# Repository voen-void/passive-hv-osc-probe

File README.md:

# Passive High Voltage oscilloscope probe

> [!IMPORTANT]
> **UNTESTED!**
> **This project is still under construction and has not yet been electrically tested. The stated voltage ratings are design targets, not verified operating limits. It is not recommended to build this currently!**

[Schematic pdf](/images/hv-probe-passive-schematic.pdf) included in the repo.

*Summary:*
This is a 1000:1 passive high-voltage oscilloscope probe designed for measurements up to 20 kV peak. The probe uses a compensated resistive/capacitive divider, a shielded and resin-potted PCB construction, and is designed to fit inside a 37.6 mm ID metal tube. (1-1/2" tubing will do fine here) The achieveable bandwidth is around XX MHz.

## TLDR
| Parameter                    | Value             |
| ---------------------------- | ----------------- |
| Attenuation                  | 1000:1            |
| Maximum recommended voltage  | 20 kV peak        |
| Divider                      | 50 MΩ / 50 kΩ     |
| Probe body                   | Resin-potted PCB  |
| Shield                       | Brass/copper tube |
| Shield inner diameter        | 37.6 mm (1.48 in) |
| PCB                          | 2-layer           |
| Recommended potting resin εr | ≤ 6               |
| Compensation                 | Adjustable        |
| bandwidth                    | XX MHz            |
| Status                       | **Not yet tested**|

The design is based on a [EEVBlog Video](https://www.youtube.com/watch?v=jUvSP3BQpvs). The electrical design is done in [KiCad](https://www.kicad.org/) 10.0.6, and the mechanical design is done in [onshape](https://www.onshape.com/en/). The total cost of a single probe adds up to around **100 USD**, though it will be larger because not all parts can be bought in small enough quantities (eg. the resin, the PCBs \[usually 5 minimum\] and the shielding tube).

> [!NOTE]
> The PCBs for this project have been provided by [PCBWay](https://www.pcbway.com/).

## What is it?
This project tackles the design of a simple high voltage oscilloscope probe based on the principles of a voltage divider. The simplest schematic would look like this:

<!--

-->

But it's a bit more complex than that if we want to probe AC signals of considerable frequency. The parasitic capacitances need to be compensated to achieve better bandwidth. For this reason the resistors forming the voltage divider are bypassed by capacitors which increase the AC transmittance of the circuit.

<!--

-->

The capacitance values presented in the above schematic are just for reference, and will likely be different for the actual probe. For a compensated probe the transmittance of just the resistors should match that of just the capacitors. If we cared only to measure DC, then the capacitors could be ommited entirely.

At the low voltage end two footprints for capacitors are provided which allow simple compensation as you will need to adjust that capacitance to achieve a flat frequency response. Capacitor values are also proposed, but the final capacitor value may differ from the proposed value because the parasitic capacitance depends on the PCB, components, potting compound and mechanical construction.
For adjusting the DC and low frequency transmittance a 10 turn potentiometer is provided. It should be set to 1 MΩ (full range) by default. While calibrating adjust it to reach desired 1000:1 division ratio. Then the capacitor should be adjusted to achieve flat frequency response. A proposed calibration procedure follows;

### Calibration

The proposed calibration procedure:
1. Set the 10-turn potentiometer to 1 MΩ.
2. Apply a suitable low-voltage signal.
3. Adjust the potentiometer until the DC attenuation is 1000:1.
4. Apply a square-wave calibration signal.
5. Adjust the compensation capacitor(s) for the flattest frequency response.
6. Verify the response at multiple frequencies.

## Safety

> [!CAUTION]
> High voltages can easily be lethal. Only deal with them if you are qualified. You are building and using this project at your own risk! This is experimental high-voltage equipment.

1. Do not use the probe on energized equipment unless you are qualified to work with high voltage.
2. The 20 kV value is currently a design target, not a verified rating.
3. Never rely on the probe alone to provide isolation.
4. Use an appropriate current-limited HV source during testing.
5. Ensure the oscilloscope and all connected equipment are rated appropriately.
6. The metal shield must be properly grounded.
7. Inspect the probe for mechanical damage before use.
8. Do not use a probe that has experienced an internal arc-over.
7. Potting compound can make internal failures difficult or impossible to inspect.

The maximum recommended voltage which this probe can measure is 20 kV **peak**. The components should handle 50 kV, but the final breakdown voltage depends on the quality of your craftsmanship - primarly the resin used, how clean the elements were when casting them in resin, if there are any air bubbles trapped inside the resin (**there shouldn't be any!**). A safety margin must be used!

### Internal arc-over protection

For increased safety a microwave fuse may be added in series with the input of the probe. This way if an over-current condition occurs - indicating an internal arc over - the fuse will open indicating thus. Microwave fuses are the highest voltage rated fuses I could cheaply find, and should do the job. A lower current fuse would be ideal, but those only come with voltage ratings up to 250 VAC. The reason for that fuse is to protect the probe in the case of an internal arc-over. If an arc over was to happen inside the probe, excessive current would be drawn from DUT (if DUT can provide it). Sustained internal arcing might lead to pressure buildup inside the probe body, which due to it's construction could become very dangerous. In an extreme scenario the probe could explode causing harm to everything around it. For this reason it is recommended to use some sort of fuse in series with the probe input, and it it blows, the probe should no longer be used and should be marked as faulty and discarded. High voltage apparatus potted in hard resin is known to pose this kind of danger and should be handled accordingly.

## Physical construction

[A drawing with the dimensions](/images/hv-probe-passive-dimensions.pdf) of the PCB included in the repo.

The probe requires some special attention when it comes to construction. Since the divider consists of such high value resistors (50 MΩ to 50 kΩ divider), it's sensitive to interference. For this reason the probe is designed to fit in a shield in the form of a brass or copper tube of the inner diameter of 37,6 mm (1.48 in). This shield shall be grounded to protect the sensitive signal inside. To increase dielectric breakdown a special resin must be used, and the PCB inside the shield should be cast in it. Since the voltages measured are significant, leaving the PCB in the free air wont cut it. Try to pick a resing with as low dielectric constant as possible. [HUNTSMAN CW5620 BLUE](https://products.huntsman.com/products/arathane-cw-5620-hy-5610) was used, which has a relative dielectric constant of 6. It is recommended to not use resins of higher relative dielectric constant as it increase the parasitic capacitances, which will degrade the bandwidth of the probe cutting down high frequency transmittance.

### Cost of building a single probe

| Element (MPN)                | Reference     | Qty.  | Price \[USD\] |
| --------------------------   | ------------- | ----- | ----------- |
| PCB                          | -             | 1     | 4.2         |
| [564RC0GAJ602EJ240J](https://mou.sr/46weVJR)           | C1-C5, C8-C12 | 10    | 30.27       |
| [VJ1206A222FFBAT](https://mou.sr/3SJN9Gu)              | C6, C7        | 2     | 2.55        |
| [112413](https://mou.sr/46wNFuQ)                       | J2            | 1     | 8.22        |
| [VR68000001005JAC00](https://mou.sr/3V2SlWK)           | R1-R5         | 5     | 7.02        |
| [CR1206-FX-5602ELF](https://mou.sr/3SBNyLk)            | R6            | 1     | 0.1         |
| [3296Z-1-105LF](https://mou.sr/4zNrIVU)                | RV1           | 1     | 2.45        |
| HUNTSMAN CW5620 BLUE Resin   | -             | 732 g | 25          |
| Copper shielding tube        | -             | 15 cm | 17          |
| 3DP filament cost            | -             | -     | 2           |

Total: 98.81 USD without shipping for a single probe. Both the PCBs, the resin and the shielding tube only come in larger quantities than needed for the project, thus the actual price may be higher depending on what you are able to source.

### PCB

The PCB has been designed to be a simple two-layer board. Soldermask has been removed from the part of the PCB that shall be submerged in isolating resin. The part of the PCB that has soldermask left should be left sticking out of the resin to allow for adjustments of the compensation capacitors and resistor if needed. A solder pad connected to probe ground is exposed to facilitate an easy connection to the shield.

The PCB has been designed with a specific kind of HV terminal construction. A large portion of copper is exposed at the HV end of the probe with a long distance separating it from the shield, to increase creepage distance. This part of the probe (tapered end) should be exposed from the shield and should be cast in resin, preferably in a ribbed shape for further increase of creepage distance. Before casting the PCB a brass piece shall be machined such that it fits over the straight tip of the tapored end of the PCB and presents a female thread at the end, into which a screw may be threaded into to make electrical contact. This piece should be soldered to the tapored tip of the PCB before casting. It should be noted that **no excessive force** should be used on this part of the probe in relation to the probe body. To make fastening easier the exposed part of the brass piece may be shaped in a way which enables holding it with an appropirately sized wrench. In such case a wrench may be used to hold the HV terminal of the probe down while fastening an attachment to it. The end piece should only be tightened finger-tight.

#### The manufactured PCB

I had the PCB manufactured by [PCBWay](https://www.pcbway.com/). The process was very simple: I uploaded the gerbers, placed a Quick Order and the PCBs (five of them!) arrived at my doorstep in a couple of days. I was pleasantly surprised by the packing quality and the PCB manufacture quality was excellent, picture below!

After receiving the PCB i shortly proceeded to populating it with components. [Assembly drawings](/images/hv-probe-passive-assembly.pdf) included in the repo.

### Notes on elements used

The resistors used for the high voltage part of the voltage divider are special high voltage resistors, which may operate up to 10 kV across them. The capacitors used in the divider are all C0G / NP0 dielectric capacitors, for increased  temperature stability. other dielectrics may be used, but it's strongly recommended to use Class I dielectric materials, preferably C0G / NP0 as it will cause the smallest drift in alignment over a wide range of temperatures.

### Casting in resin

To cast the probe in resin a CAD model for a 3D-printable mold has been made in [onshape](https://cad.onshape.com/documents/634b2c7804eb6959816cbee4/w/1f30c7d8f223e5e8fad3fc6d/e/e251d38d61b503254921d7bb). 

<!--

-->

Recommended material for the mold is PETG, as it's recommended for molding and should allow for easier separation after casting. The two mold halves are to be screwed together by 18 70 mm long M4 bolts. Wax was used as mold release. The resin should be poured down into the metal tube, with the tip of the probe facing downwards. Resin should be added until it fills up the mold up to the top 3 mm venting holes.

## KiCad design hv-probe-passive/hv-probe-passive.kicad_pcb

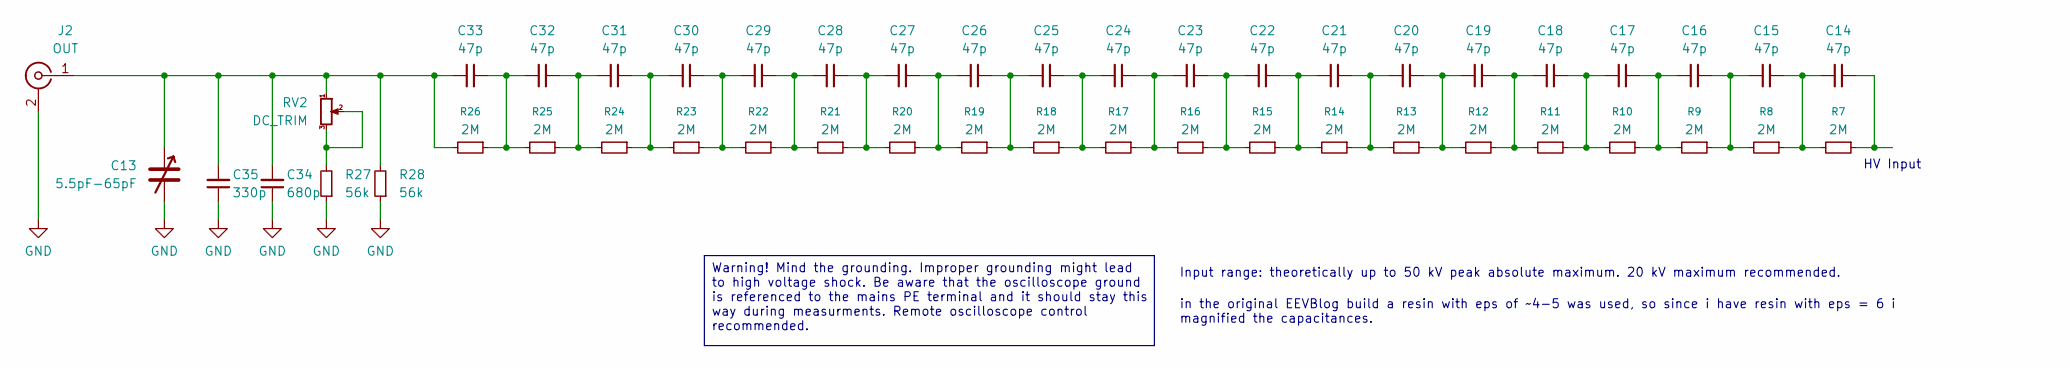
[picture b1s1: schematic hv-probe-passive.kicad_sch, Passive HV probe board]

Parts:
C13: 5.5pF-65pF; BFC2808 P5.0x7.5mm; LCSC C3273327
C14, C15, C16, C17, C18, C19, C20, C21, C22, C23, C24, C25, C26, C27, C28, C29, C30, C31, C32, C33: 47p; C_1808_4520Metric; LCSC C2958815
C34: 680p; C_1206_3216Metric; MPN AC1206JRNPOBBN681; LCSC C3871624
C35: 330p; C_1206_3216Metric; MPN 1206CG331J101NT
J2: OUT; BNC_Amphenol_B6252HB-NPP3G-50_Horizontal; MPN 112413
R7, R8, R9, R10, R11, R12, R13, R14, R15, R16, R17, R18, R19, R20, R21, R22, R23, R24, R25, R26: 2M; R_2512_6332Metric; LCSC C2779442
R27, R28: 56k; R_0805_2012Metric; LCSC C17756
RV2: DC_TRIM; Potentiometer_Bourns_3296X_Horizontal; LCSC C49190482

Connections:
GND: C13.2, C34.1, C35.1, J2.2 (Ext), R27.1, R28.1
unnamed: C14.1, R7.1
unnamed: C14.2, C15.1, R7.2, R8.1
unnamed: C15.2, C16.1, R8.2, R9.1
unnamed: C16.2, C17.1, R9.2, R10.1
unnamed: C17.2, C18.1, R10.2, R11.1
unnamed: C18.2, C19.1, R11.2, R12.1
unnamed: C19.2, C20.1, R12.2, R13.1
unnamed: C20.2, C21.1, R13.2, R14.1
unnamed: C21.2, C22.1, R14.2, R15.1
unnamed: C22.2, C23.1, R15.2, R16.1
unnamed: C23.2, C24.1, R16.2, R17.1
unnamed: C24.2, C25.1, R17.2, R18.1
unnamed: C25.2, C26.1, R18.2, R19.1
unnamed: C26.2, C27.1, R19.2, R20.1
unnamed: C27.2, C28.1, R20.2, R21.1
unnamed: C28.2, C29.1, R21.2, R22.1
unnamed: C29.2, C30.1, R22.2, R23.1
unnamed: C30.2, C31.1, R23.2, R24.1
unnamed: C31.2, C32.1, R24.2, R25.1
unnamed: C32.2, C33.1, R25.2, R26.1
unnamed: C13.1, C33.2, C34.2, C35.2, J2.1 (In), R26.2, R28.2, RV2.1
unnamed: R27.2, RV2.2, RV2.3

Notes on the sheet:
HV Input
in the original EEVBlog build a resin with eps of ~4-5 was used, so since i have resin with eps = 6 i magnified the capacitances.
Warning! Mind the grounding. Improper grounding might lead to high voltage shock. Be aware that the oscilloscope ground is referenced to the mains PE terminal and it should stay this way during measurments. Remote oscilloscope control recommended.
Input range: theoretically up to 50 kV peak absolute maximum. 20 kV maximum recommended.

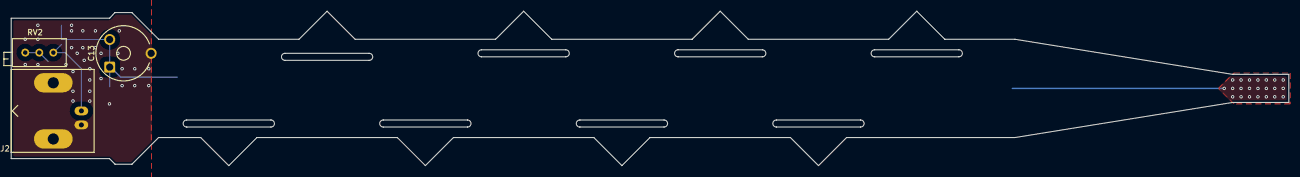
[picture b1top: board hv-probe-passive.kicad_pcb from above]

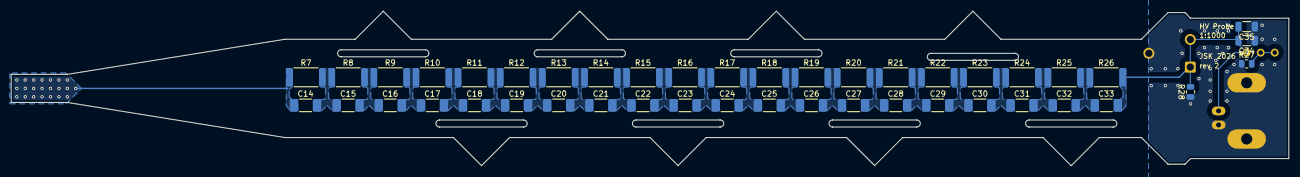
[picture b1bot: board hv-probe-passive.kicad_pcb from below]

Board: 2 copper layers, 231.1 x 27.9 mm, 47 parts (44 on the bottom side), 23 nets.

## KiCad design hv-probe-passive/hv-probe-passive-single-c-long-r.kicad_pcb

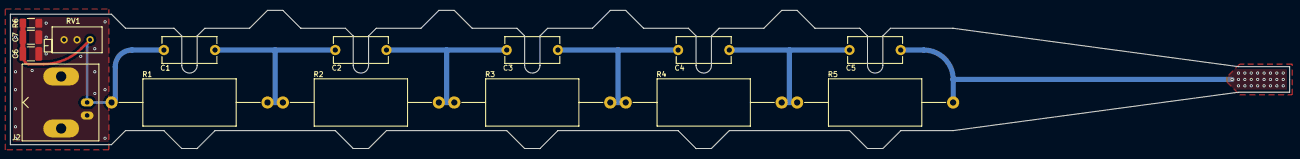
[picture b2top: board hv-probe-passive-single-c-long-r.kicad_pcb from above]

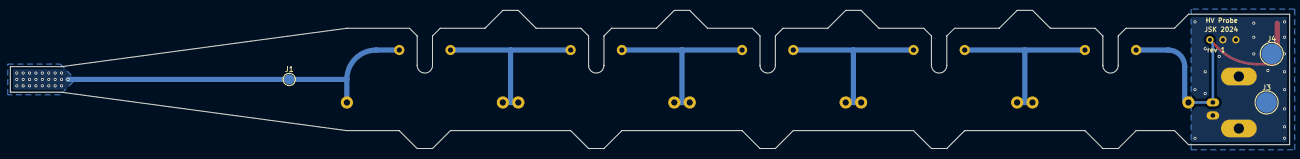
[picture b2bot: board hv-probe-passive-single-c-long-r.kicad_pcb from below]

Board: 2 copper layers, 250.0 x 27.0 mm, 18 parts (3 on the bottom side), 7 nets.

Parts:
C1, C2, C3, C4, C5: 22p; C_Disc_D10.5mm_W5.0mm_P10.00mm
C6, C7: 2n2; C_1210_3225Metric_Pad1.33x2.70mm_HandSolder
J1: IN; TestPoint_Pad_D2.0mm
J2: OUT; BNC_Amphenol_B6252HB-NPP3G-50_Horizontal
J3, J4: GND; TestPoint_Pad_D4.0mm
R1, R2, R3, R4, R5: 10M; R_Axial_DIN0918_L18.0mm_D9.0mm_P30.48mm_Horizontal
R6: 56k; C_1206_3216Metric_Pad1.33x1.80mm_HandSolder
RV1: TRIM; Potentiometer_Bourns_3296X_Horizontal

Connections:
GND: C6.1, C7.1, J2.2 (Ext), J3.1, J4.1, R6.1, RV1.2, RV1.3
unnamed: C1.2, C2.1, R1.2, R2.1
unnamed: C2.2, C3.1, R2.2, R3.1
unnamed: C3.2, C4.1, R3.2, R4.1
unnamed: C4.2, C5.1, R4.2, R5.1
unnamed: C5.2, J1.1, R5.2
unnamed: C1.1, C6.2, C7.2, J2.1 (In), R1.1, R6.2, RV1.1

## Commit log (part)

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2024-11-20 Update README.md
    first update
2024-11-20 added kicad project files
2024-11-21 rearrange README.md
    minor rearrangement
2024-11-21 added 2 images to the documentation
2024-11-21 made information on the schematic consistent with that in the readme
2024-11-21 expanded the readme
2024-11-21 updated renderings of the pcb and the schematic
2024-12-08 added a script for rough estimation of internal capacitance, corrected schematic
2024-12-09 restoring the readme, small updates to its content
2024-12-09 expanded the warnings in the readme, added a note on pcbway sponsorship
2025-01-05 added rendered images of the pcb to the repo
2025-01-05 improvements to the capacitance estimation script, the outputs have been made more readable and comments have been added to explain the reasoning behind it.
2025-01-05 additional info about possible capacitor replacements for the hv divider
